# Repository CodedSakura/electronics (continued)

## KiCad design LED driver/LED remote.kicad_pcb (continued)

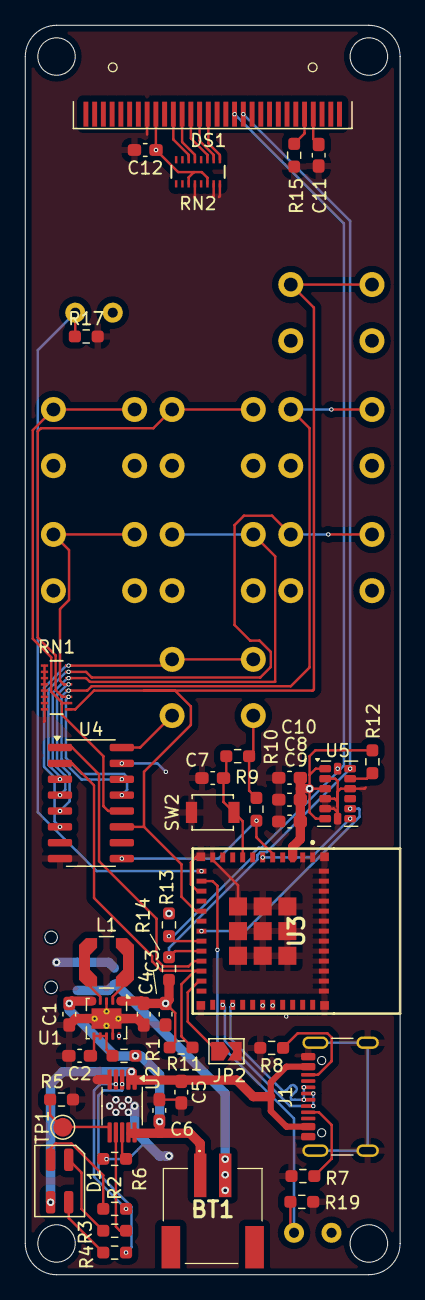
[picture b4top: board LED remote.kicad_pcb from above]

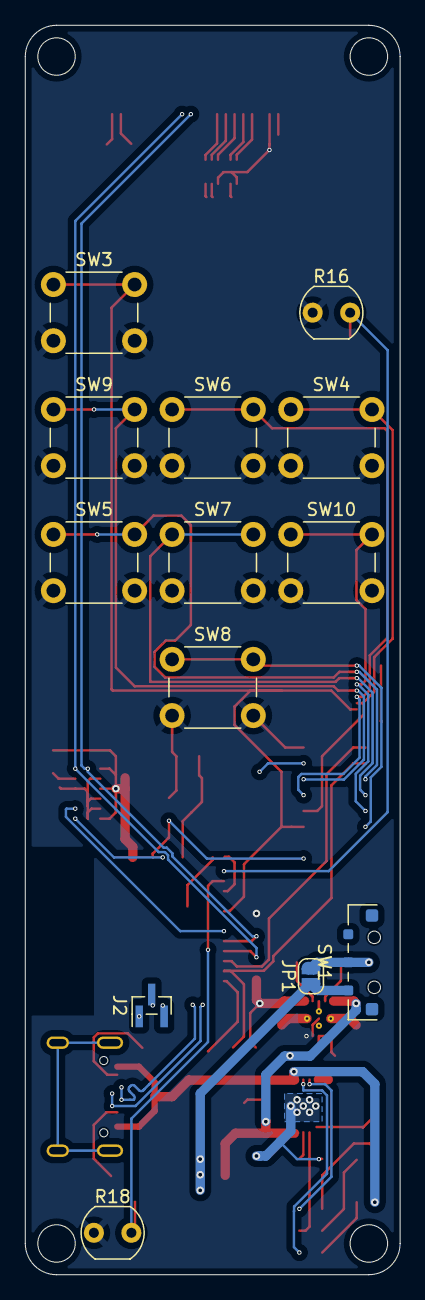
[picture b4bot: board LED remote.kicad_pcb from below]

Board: 2 copper layers, 30.0 x 100.0 mm, 57 parts (13 on the bottom side), 49 nets.

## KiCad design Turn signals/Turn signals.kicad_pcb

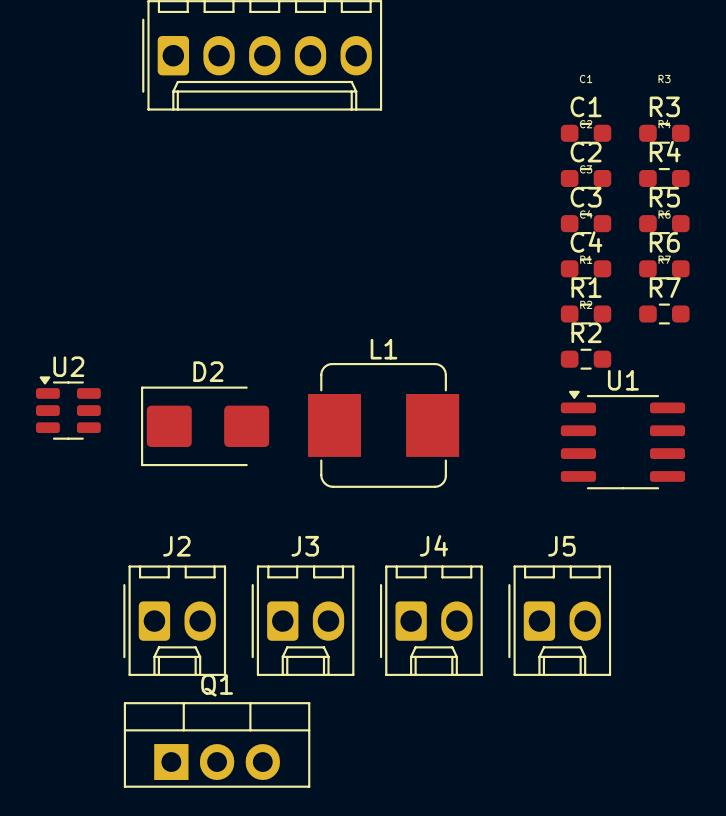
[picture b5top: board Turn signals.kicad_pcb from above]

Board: 2 copper layers, 22 parts (1 on the bottom side), 14 nets, no tracks yet.

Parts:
BT1: CR2032; BatteryHolder_multicomp_CH28-2032LF
C1, C3, C4: C; 0603_1608Metric_Pad_HandSolder_Valuea
C2: 10nF; 0603_1608Metric_Pad_HandSolder_Valuea
D2: B230; D_SMB
J2: Conn_FWD_L; Molex_KK-254_AE-6410-02A_1x02_P2.54mm_Vertical
J3: Conn_BWD_L; Molex_KK-254_AE-6410-02A_1x02_P2.54mm_Vertical
J4: Conn_FWD_R; Molex_KK-254_AE-6410-02A_1x02_P2.54mm_Vertical
J5: Conn_BWD_R; Molex_KK-254_AE-6410-02A_1x02_P2.54mm_Vertical
J6: Conn_SW; Molex_KK-254_AE-6410-05A_1x05_P2.54mm_Vertical
L1: L; L_Bourns_SRP7028A_7.3x6.6mm
Q1: IRLZ44N; TO-220-3_Vertical
R1, R2, R3, R4, R6, R7: R; 0603_1608Metric_Pad_HandSolder_Valuea
R5: 0; R_0603_1608Metric_Pad0.98x0.95mm_HandSolder
U1: ICM7555xB; SOIC-8_3.9x4.9mm_P1.27mm
U2: MT3608; SOT-23-6

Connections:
+3V0: BT1.1 (+), C3.1, J6.1, J6.5, L1.1, R5.2, U2.5 (IN)
/LED_L: J2.2, J3.2, J6.2
/LED_R: J4.2, J5.2, J6.3
EN_OUT: J6.4, U1.4 (RESET), U2.4 (EN)
GND: BT1.2 (-), C1.2, C2.2, C3.2, C4.2, Q1.3 (S), R4.2, R6.2, U1.1 (GND), U2.2 (GND)
unnamed: D2.2 (A), L1.2, U2.1 (SW)
unnamed: J2.1, J3.1, J4.1, J5.1, Q1.2 (D)
unnamed: Q1.1 (G), R7.2
unnamed: C2.1, U1.5 (CTRL)
unnamed: R1.2, R2.1, U1.7 (DIS)
unnamed: R6.1, R7.1, U1.3 (OUT)
unnamed: C1.1, R2.2, U1.2 (TRIG), U1.6 (THR)
unnamed: R3.2, R4.1, U2.3 (FB)
VCC: C4.1, D2.1 (K), R1.1, R3.1, R5.1, U1.8 (VCC)

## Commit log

2024-03-28 led driver: schematic, most of pcb
2024-03-29 update led driver, add turn signals
2024-04-01 update LED driver
2024-04-03 remove backups from git
2024-04-04 led driver
2024-04-04 work on LED driver (WIP)
2024-04-04 mostly finish led driver
2024-04-05 towel machine motor driver
2024-04-07 led driver parts
2024-04-11 2024-04-11
2024-04-15 2024-04-13
2024-04-16 2024-04-16
2024-04-17 2024-04-17
2024-04-18 2024-04-18
2024-06-04 2024-06-04 001
2024-06-04 2024-06-04 002
2024-06-13 2024-06-05
2024-11-23 2024-11-23
2024-11-24 2024-11-24 (sub-par pcb)
2024-11-24 2024-11-24 (better pcb)
2025-02-06 led matrix primitive implementation
2025-02-07 2025-02-07
2025-04-03 poe splitter 2025-04-03
